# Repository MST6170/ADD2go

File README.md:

# ADD2go

**Wireless Fernanzeige für Dinamica Generale ADD2 / Siloking Mischwagen**

Überträgt Gewichtsdaten kabellos von der Mischwagen-Waage zum Radlader-Display oder Smartphone.

ADD2go ist in erster Linie eine **Fernanzeige** für die ADD2 Waage. Zusätzlich integriert ist eine **Schaufel-Wiegung** mit Drucksensor — fand ich nützlich, daher ist sie mit reingewandert.

*ADD2go — kabellose Fernanzeige für die ADD2-Waage*

---

## 📋 Übersicht

ADD2go besteht aus zwei ESP32-Modulen und einer optionalen WebApp:

| Modul | Standort | Funktion |
|-------|----------|----------|
| **Sender** | Mischwagen | Liest RS232 von ADD2 Waage, sendet per WiFi |
| **Empfänger** | Radlader | Zeigt Gewicht auf TFT-Display an |
| **WebApp** | Smartphone | Gewicht im Browser anzeigen |

> 💡 **Hinweis zur Hardware:** Sender und Empfänger nutzen **dieselbe Platine** — sie wird je nach Anwendung unterschiedlich bestückt (Sender: MAX3232 + WI-NET; Empfänger: zusätzlich TFT-Header, ADS1115-Header, K7812M für Drucksensor). Details siehe [`add2go_pcb/README.md`](add2go_pcb/README.md).

### Features

**Sender:**
- ✅ RS232 Auswertung des ADD2 Protokolls
- ✅ WiFi Access Point ("ADD2go")
- ✅ WiFi-Manager - zusätzlich mit Heimnetz verbinden
- ✅ mDNS - erreichbar unter `http://add2go.local`
- ✅ UDP Broadcast für Hardware-Empfänger
- ✅ WebSocket Server für WebApp
- ✅ Eingebaute WebApp mit TOTAL/ZERO Funktion
- ✅ "OFF" Erkennung wenn Waage ausgeschaltet
- ✅ Hardware Watchdog (kein Aufhängen)

**Empfänger:**
- ✅ Echtzeit-Gewichtsanzeige
- ✅ TOTAL/ZERO Funktion (Auto-Reset bei Verbindungsverlust)
- ✅ Schaufel-Wiegung mit Drucksensor (optional)
- ✅ Filter für stabile Anzeige (Mittelwert + Hysterese)
- ✅ ADS1115-Watchdog (Sensor-Ausfall wird erkannt)
- ✅ Auto-Reconnect bei WiFi-Verlust
- ✅ Hardware Watchdog

---

## 🌐 WiFi-Manager

Der Sender kann sich zusätzlich mit einem externen WLAN (z.B. Hof-WLAN) verbinden. Dadurch muss das Handy nicht mehr ins "ADD2go" WLAN wechseln.

### Einrichtung

1. Handy mit WLAN **"ADD2go"** verbinden
2. Browser öffnen: `http://192.168.4.1/setup`
3. Verfügbare Netzwerke werden angezeigt
4. Netzwerk auswählen, Passwort eingeben
5. Nach erfolgreicher Verbindung: erreichbar unter `http://add2go.local`

### Betriebsmodi

| Modus | Beschreibung |
|-------|--------------|
| **Nur AP** | Standard - Sender erstellt eigenes WLAN "ADD2go" |
| **AP + Station** | Sender ist zusätzlich mit Heimnetz verbunden |

### Vorteile der Heimnetz-Verbindung

- Kein WLAN-Wechsel mehr nötig am Handy
- Erreichbar unter `http://add2go.local` (mDNS)
- WLAN-Daten werden gespeichert (überlebt Neustart)
- Auto-Reconnect wenn Mischwagen zurückkommt
- AP "ADD2go" bleibt zusätzlich aktiv (Fallback)

---

## 🔧 Hardware

### Sender (Mischwagen)

*Sender-Modul: ESP32, MAX3232 (RS232) und 7805-Spannungsregler*

| Komponente | Typ | Bemerkung |
|------------|-----|-----------|
| Mikrocontroller | [ESP32-WROOM-32U](https://www.amazon.de/dp/B0F65KPWYR) | Mit U.FL Antennenanschluss |
| Antenne | 2.4GHz extern | Im ESP32-Set enthalten |
| RS232 Wandler | MAX3232CPE | DIP-16, 5x 1µF Kondensatoren |
| Spannungsregler | K7805M | 12V → 5V Schaltregler (pin-kompatibel zu 7805, kein Kühlkörper nötig) |
| Verpolschutz | 1N5822 | Schottky-Diode |
| Überspannungsschutz | 1.5KE18A | TVS-Diode 18V |
| WI-NET Stecker | Binder M16 5-pol | Bestellnr. 09 0313 00 05 |
| Gehäuse | [Industrie-Gehäuse 100×68×50 mm](https://de.aliexpress.com/item/1005005622148025.html) | gekauft (kein 3D-Druck nötig) |
| Platine | Custom KiCad-Projekt | Schaltplan, Layout, Fertigung — siehe [`add2go_pcb/README.md`](add2go_pcb/README.md) |

**Pinbelegung Sender:**

| ESP32 Pin | Funktion |
|-----------|----------|
| GPIO16 | RX2 ← MAX3232 (Daten von Waage) |
| GPIO17 | TX2 → MAX3232 (nicht verwendet) |
| 5V | Versorgung vom Spannungsregler |
| GND | Gemeinsame Masse |

*ESP32-WROOM-32 Pinbelegung (Referenz)*

### Empfänger (Radlader)

*Empfänger-Modul: ESP32, ILI9341 Display mit Touch und ADS1115 ADC*

| Komponente | Typ | Bemerkung |
|------------|-----|-----------|
| Mikrocontroller | [ESP32-WROOM-32U](https://www.amazon.de/dp/B0F65KPWYR) | Mit U.FL Antennenanschluss |
| Antenne | 2.4GHz extern | Im ESP32-Set enthalten |
| Display | [ILI9341 3.2" TFT](https://de.aliexpress.com/item/1005003005216533.html) | 320x240, SPI, mit Touch |
| Touch | XPT2046 | Resistiv, im Display integriert |
| ADC | ADS1115 | 16-bit, I²C (für Schaufel-Wiegung) |
| Drucksensor | [XIDIBEI 0-300 bar](https://de.aliexpress.com/item/4001002862246.html) | 9-36V Versorgung, 0.5-4.5V Ausgang (für Schaufel-Wiegung, optional) |
| Reed-Kontakt | Digital | Wiegeposition erkennen (optional) |
| Spannungsregler 5 V | K7805M | 12 V → 5 V Schaltregler (für ESP32) |
| Spannungsregler 12 V | K7812M | stabilisierte 12 V (für Drucksensor) |
| Gehäuse | 3D-gedruckt | STL-Dateien, Schalter, Kabelverschraubung — siehe [`case/README.md`](case/README.md) |
| Platine | Custom KiCad-Projekt | Schaltplan, Layout, Fertigung — siehe [`add2go_pcb/README.md`](add2go_pcb/README.md) |

**Pinbelegung Empfänger:**

| ESP32 Pin | Funktion |
|-----------|----------|
| GPIO5 | Display CS |
| GPIO2 | Display RST |
| GPIO4 | Display DC |
| GPIO23 | SPI MOSI |
| GPIO18 | SPI SCK |
| GPIO19 | SPI MISO |
| GPIO15 | Touch CS |
| GPIO14 | Touch IRQ |
| GPIO21 | I²C SDA (ADS1115) |
| GPIO22 | I²C SCL (ADS1115) |
| GPIO36 | Reed-Kontakt (LOW = Wiegeposition) |

*XIDIBEI Drucksensor (0–300 bar, 9–36 V → 0,5–4,5 V) — Quelle für die Schaufel-Wiegung*

### WI-NET Stecker (ADD2 Waage)

Der WI-NET Anschluss ist ein 5-poliger M16 Stecker an der ADD2 Waage.

**Passender Kabelstecker:** [Binder Serie 680, M16, 5-polig](https://www.binder-connector.de/de/produkte/rundsteckverbinder/m16-ip40-serie-680/kabelstecker-09-0313-00-05)
- Bestellnummer: **09 0313 00 05**
- Lötkontakte, 3.0-6.0mm Kabeldurchlass

> 💡 **Hinweis:** Bei diesem Stecker bin ich mir nicht 100% sicher — er passt nicht ganz exakt in die Buchse, funktioniert aber zuverlässig.

Die Pinbelegung wurde durch eigene Messungen ermittelt:

| Pin | Position | Funktion | Verbindung |
|-----|----------|----------|------------|
| 1 | unten | +12V | → Spannungsregler VIN |
| 2 | rechts oben | GND | → Gemeinsame Masse |
| 3 | oben mitte | TX | → MAX3232 R1IN (Pin 13) |
| 4 | links oben | - | nicht belegt |
| 5 | links unten | - | nicht belegt |

*WI-NET Stecker (Binder M16, 5-polig) — eigene Messung der Pinbelegung*

> ⚠️ **Wichtig:** Pinbelegung von vorne auf die Buchse (an der Waage) gesehen!

---

## 📡 Kommunikation

### WiFi Konfiguration

| Parameter | Wert |
|-----------|------|
| AP SSID | `ADD2go` |
| AP Passwort | keins (offen) |
| AP IP | `192.168.4.1` |
| AP Subnetz | `255.255.255.0` |
| mDNS Hostname | `add2go.local` |
| WiFi Modus | APSTA (AP + Station gleichzeitig) |

### Netzwerk-Protokolle

| Protokoll | Port | Richtung | Verwendung |
|-----------|------|----------|------------|
| UDP Broadcast | 5005 | Sender → Empfänger | Hardware-Display |
| WebSocket | 81 | Sender ↔ Browser | WebApp (bidirektional) |
| HTTP | 80 | Browser → Sender | WebApp + Setup-Seite |

### UDP Protokoll (für Hardware-Empfänger)

Der Sender sendet alle 100ms (10 Hz) einen UDP-Broadcast:

| Parameter | Wert |
|-----------|------|
| Ziel-IP | `192.168.4.255` (Broadcast) |
| Port | `5005` |
| Format | ASCII String |

**Nachrichten:**

| Nachricht | Bedeutung |
|-----------|-----------|
| `1234` | Gewicht in kg (ohne Einheit) |
| `OFF` | Waage ist ausgeschaltet |

### WebSocket Protokoll (für WebApp)

Der Sender sendet alle 100ms (10 Hz) an alle verbundenen WebSocket-Clients:

| Parameter | Wert |
|-----------|------|
| Port | `81` |
| Format | `Gewicht\|RSSI` |

**Beispiele:**

| Nachricht | Bedeutung |
|-----------|-----------|
| `1234\|-65` | 1234 kg, Signalstärke -65 dBm |
| `OFF\|-70` | Waage aus, Signalstärke -70 dBm |

---

## 📟 RS232 Protokoll (ADD2 Waage)

Das RS232 Protokoll wurde durch eigenes Reverse-Engineering ermittelt.

### Schnittstellenparameter

| Parameter | Wert |
|-----------|------|
| Baudrate | 19200 |
| Datenbits | 8 |
| Parität | Keine |
| Stoppbits | 1 |
| Updaterate | ~1.3 Hz (alle ~770ms) |

### Frame-Struktur

Die Waage sendet kontinuierlich Frames mit folgendem Aufbau:

```
[Präambel] [Start] [Type] [Seq] [Header] [Gewicht ASCII] [Ende]
    16       0x23   0x03   xx    0x18 0x00    "  1234"     0x0A
```

| Feld | Bytes | Wert | Beschreibung |
|------|-------|------|--------------|
| Präambel | 16 | variabel | Sync-Bytes (werden ignoriert) |
| Start | 1 | `0x23` | Start-Marker (`#`) |
| Type | 1 | `0x03` | Frame-Typ (ETX) |
| Sequence | 1 | `0x00-0xFF` | Laufender Zähler |
| Header | 2 | `0x18 0x00` | Fester Header |
| Gewicht | variabel | ASCII | Rechtsbündig mit Leerzeichen |
| Ende | 1 | `0x0A` | Line Feed (LF) |

### Beispiel-Frame

```
Hex:  23 03 7B 18 00 20 20 20 20 32 0A
      │  │  │  │  │  └──────────┴──┴── "    2" + LF = 2 kg
      │  │  │  └──┴── Header 0x18 0x00
      │  │  └── Sequence 0x7B (123)
      │  └── Type 0x03
      └── Start 0x23
```

### Gewichtswerte

| Anzeige Waage | RS232 Daten | Bedeutung |
|---------------|-------------|-----------|
| `2` | `20 20 20 20 32` | 2 kg |
| `123` | `20 20 31 32 33` | 123 kg |
| `1234` | `20 31 32 33 34` | 1234 kg |
| (aus) | keine Daten | Waage ausgeschaltet |

### OFF-Erkennung

Wenn 3 Sekunden lang keine gültigen RS232-Daten empfangen werden, gilt die Waage als ausgeschaltet. Der Sender sendet dann `"OFF"` über UDP und WebSocket.

---

## 💾 Installation

### Voraussetzungen

- Arduino IDE 1.8.19
- ESP32 Board Package (v3.x empfohlen)
- USB-Treiber für ESP32 (CP2102 oder CH340)

### Benötigte Libraries

**Sender:**
- WebSockets by Markus Sattler (Library Manager: "WebSockets")

**Empfänger:**
- TFT_eSPI by Bodmer
- XPT2046_Touchscreen by Paul Stoffregen
- Adafruit ADS1X15 by Adafruit

### TFT_eSPI Konfiguration

Die TFT_eSPI Library muss für das ILI9341 Display konfiguriert werden.

> ⚠️ **Wichtig:** Die TFT_eSPI Library hat eine **globale** Konfigurationsdatei (`User_Setup.h`). Diese wird von ALLEN Projekten geteilt, die TFT_eSPI verwenden! Wenn du an einem anderen Projekt arbeitest und die Pins änderst, läuft ADD2go nicht mehr — `tft.init()` hängt dann beim Boot ohne Fehlermeldung. **Daher: vor jedem Flashen prüfen, dass `User_Setup.h` zu ADD2go passt.**

**Datei:** `Arduino/libraries/TFT_eSPI/User_Setup.h`

```cpp
// Display-Treiber
#define ILI9341_DRIVER

// Display-Größe
#define TFT_WIDTH  240
#define TFT_HEIGHT 320

// Pin-Definitionen
#define TFT_CS   5
#define TFT_DC   4
#define TFT_RST  2
#define TFT_MOSI 23
#define TFT_SCLK 18
#define TFT_MISO 19

// SPI-Geschwindigkeit
#define SPI_FREQUENCY 40000000

// Touch
#define TOUCH_CS 15
```

### Flashen

**Sender:**
```
Board:     ESP32 Dev Module
Datei:     add2go_sender_v1_2_4/add2go_sender_v1_2_4.ino
Baudrate:  115200
```

**Empfänger:**
```
Board:     ESP32 Dev Module
Datei:     add2go_empfaenger_v1_0_2/add2go_empfaenger_v1_0_2.ino
Baudrate:  115200
```

---

## 🖥️ Bedienung

### Hardware-Display (Empfänger)

*Hauptansicht mit Gewichtszahl und TOTAL/ZERO-Buttons*

**Anzeigen:**

| Anzeige | Farbe | Bedeutung |
|---------|-------|-----------|
| Gewicht | Weiß | Normale Anzeige |
| `OFF` | Rot | Waage ausgeschaltet |
| `OFFLINE` | Rot | Keine WiFi-Verbindung zum Sender |
| `SUCHE..` | Orange | WiFi wird gesucht |
| `- - - -` | Grau | Verbunden, warte auf Daten |

**Buttons:**

| Button | Funktion |
|--------|----------|
| **TOTAL** | Zeigt Gesamt-Gewicht von Waage |
| **ZERO** | Setzt aktuelles Gewicht als Null (Differenz-Messung) |
| **Schaufel** | Öffnet Schaufel-Wiegung Menü |

> 💡 **Hinweis:** ZERO wird automatisch zurückgesetzt wenn die Verbindung zum Sender verloren geht oder die Waage auf OFF wechselt. So gibt es nach Wiedereinschalten keinen falschen Offset.

**Schaufel-Wiegung Menü:**

*Setup-Menü für die Schaufel-Wiegung*

| Menüpunkt | Funktion |
|-----------|----------|
| TARA | Setzt leere Schaufel als Nullpunkt |
| KALIBRIEREN | Bekanntes Gewicht eingeben zur Kalibrierung |
| FILTER | Mittelwert-Anzahl (5-30) und Hysterese-Schwelle (1-10 kg) |
| ZURÜCK | Zurück zur Hauptansicht |

> 💡 **Hinweis:** Bei TARA und Kalibrierung wird der Filter-Buffer automatisch geleert, damit die Anzeige sofort die neuen Werte zeigt.

**Sensor-Ausfall:** Wenn der ADS1115 nicht antwortet (z.B. Kabelbruch, Wackelkontakt), zeigt der Schaufel-Button `SENSOR-FEHLER` in rot an. TARA und KALIBRIEREN sind dann gesperrt.

---

## 📱 WebApp

Der Sender bietet eine eingebaute WebApp - das Gewicht direkt auf dem Smartphone anzeigen. Sie funktioniert parallel zum Hardware-Empfänger und ist als Nebenfunktion gedacht.

<p align="center">
  
  <br>
  <em>WebApp im Browser am Smartphone</em>
</p>

### Zugriff

| Methode | URL | Wann nutzen |
|---------|-----|-------------|
| Direkt | `http://192.168.4.1` | Handy mit "ADD2go" WLAN verbunden |
| Heimnetz | `http://add2go.local` | Handy im Hof-WLAN (nach Setup) |
| Heimnetz | `http://[IP-Adresse]` | Falls mDNS nicht funktioniert |

### Funktionen

| Element | Beschreibung |
|---------|--------------|
| **Gewichtsanzeige** | Groß und zentral, mit "kg" Einheit |
| **TOTAL** | Zeigt Gesamtgewicht von der Waage |
| **ZERO** | Speichert aktuelles Gewicht, zeigt Differenz |
| **Signalstärke** | 📶▂▄▆█ (4 Stufen) |
| **Status** | 🟢 Verbunden / 🟠 Waage aus / 🔴 Offline |

### TOTAL / ZERO Funktion

- **TOTAL**: Normaler Modus - zeigt das Gewicht wie es von der Waage kommt
- **ZERO**: Drücken um aktuelles Gewicht als Nullpunkt zu setzen. Danach wird die Differenz angezeigt. Praktisch zum Wiegen von Zuladungen.

Der aktive Modus ist **orange** markiert. Diese Funktion läuft lokal in der WebApp und beeinflusst nicht die ADD2 Waage selbst.

---

## 🔍 Troubleshooting

### Häufige Probleme

| Problem | Ursache | Lösung |
|---------|---------|--------|
| Boot-Loop, hängt bei `tft.init()` | Falsches `User_Setup.h` (z.B. von anderem Projekt überschrieben) | `User_Setup.h` der TFT_eSPI Library prüfen, Pins müssen zu ADD2go passen |
| Display zeigt `OFFLINE` | Kein WiFi zum Sender | Sender einschalten, Nähe prüfen, Antennen prüfen |
| Display zeigt `OFF` | Waage ausgeschaltet | ADD2 Waage einschalten |
| Display zeigt `- - - -` | WiFi ok, aber keine Daten | RS232 Verkabelung prüfen |
| Schaufel: `SENSOR-FEHLER` | ADS1115 antwortet nicht | I²C Verkabelung prüfen, Neustart |
| WebApp zeigt `---` | WebSocket nicht verbunden | Seite neu laden, WLAN prüfen |
| WebApp Buttons grau | Keine Verbindung | Warten oder Seite neu laden |
| `add2go.local` geht nicht | mDNS Problem | IP-Adresse direkt verwenden |
| WLAN-Daten nicht gespeichert | NVS Fehler | Serial Monitor prüfen |
| Sender startet neu | Watchdog | Serial Monitor auf Fehler prüfen |

### Serial Monitor Debug

Baudrate: **115200**

**Sender Startup (normal):**
```
========================================
ADD2go Sender - v1.2.4
========================================

[NVS] Lade gespeicherte Daten...
[NVS] SSID: MeinHofWLAN
[NVS] Passwort: (gespeichert)
[NVS] Auto-Connect: JA
[OK] RS232 gestartet (19200 Baud, GPIO16)
[OK] Watchdog: 10 Sekunden
[OK] WiFi AP gestartet: ADD2go
[OK] AP IP: 192.168.4.1
[STA] Verbinde mit: MeinHofWLAN
....
[STA] Verbunden! IP: 192.168.1.38
[OK] mDNS: http://add2go.local
[OK] UDP Port: 5005
[OK] WebServer gestartet (Port 80)
[OK] WebSocket gestartet (Port 81)

=========== ZUGRIFF ===========
Im ADD2go WLAN:
  WebApp:  http://192.168.4.1
  Setup:   http://192.168.4.1/setup

Im Heimnetz (mDNS):
  WebApp:  http://add2go.local
  Setup:   http://add2go.local/setup
  oder:    http://192.168.1.38
===============================

Warte auf ADD2 Waage...
```

**Sender Betrieb:**
```
[RS232] Gewicht: 1234 kg
[UDP] Gesendet: "1234" (1 AP Clients)
[WS] Client #0 verbunden
[STATUS] AP Clients: 1 | WS Clients: 1 | STA: MeinHofWLAN (192.168.1.38)
```

**Empfänger Startup:**
```
========================================
ADD2go Empfaenger - v1.0.1
========================================

[OK] Reed-Kontakt GPIO36 konfiguriert
[OK] ADS1115 gefunden
[OK] NVS geladen - Tara: 0.500V, Faktor: 100.0 kg/V
[OK] Display initialisiert
[OK] Touch initialisiert
[OK] Watchdog: 5 Sekunden
[OK] WiFi verbunden! IP: 192.168.4.2
[OK] UDP Port: 5005
```

---

## 📁 Projektstruktur

```
ADD2go/
├── add2go_sender_v1_2_4/
│   └── add2go_sender_v1_2_4.ino         # Sender Firmware
├── add2go_empfaenger_v1_0_2/
│   └── add2go_empfaenger_v1_0_2.ino     # Empfänger Firmware
├── add2go_pcb/                           # KiCad-Projekt für die Universal-Platine (Sender / Empfänger)
├── case/                                 # 3D-Druck-STLs für Empfänger-Gehäuse
├── images/                               # Bilder & Pinout-Diagramme
├── User_Setup.h                          # TFT_eSPI-Vorlage (in Library kopieren)
├── CLAUDE.md                             # Kurzdoku für KI-Assistenten
├── README.md                             # Diese Dokumentation
├── LICENSE                               # CC BY-NC-SA 4.0
└── .gitignore                            # Git Ignore-Liste
```

---

## 📜 Changelog

### Sender

#### v1.2.4 (Januar 2026)
- Fix: Watchdog früher initialisieren (vor WLAN-Warteschleife)
- Fix: idle_core_mask konservativer (nur loopTask überwachen)
- Fix: JSON SSID Escaping bei Sonderzeichen

#### v1.2.3 (Januar 2026)
- WebApp: TOTAL/ZERO Buttons hinzugefügt
- WebApp: Gewicht mit "kg" Einheit
- WebApp: Cleaner UI

#### v1.2.2 (Januar 2026)
- mDNS Support (`http://add2go.local`)
- Warten auf WLAN-Verbindung beim Boot (max 15 Sek)
- Bessere Debug-Ausgaben für NVS

#### v1.2.1 (Januar 2026)
- Async WLAN-Scan (verhindert Watchdog-Trigger)
- Robustere loop() mit mehrfachen WDT-Resets
- RS232 Byte-Limit pro Loop (max 256)

#### v1.2.0 (Januar 2026)
- WiFi-Manager WebUI unter `/setup`
- APSTA Modus (AP + Station gleichzeitig)
- WLAN-Daten persistent in NVS gespeichert
- Auto-Reconnect bei Verbindungsverlust

#### v1.1.0 (Januar 2026)
- WebSocket Server für Browser/Handy
- Eingebettete WebApp
- Signalstärke-Anzeige

#### v1.0.0 (Januar 2026)
- Erste stabile Release
- RS232 Protokoll-Auswertung
- UDP Broadcast
- Hardware Watchdog
- OFF-Erkennung

### Empfänger

#### v1.0.2 (Mai 2026)
- NEU: Signalstärke-Anzeige (4 Balken) links vom WiFi-Status-Punkt
- Fix: SENSOR-FEHLER-Anzeige passt jetzt in den Schaufel-Button (zentriert, ohne "Schaufel:"-Präfix)

#### v1.0.1 (Mai 2026)
- Fix: ZERO-Modus wird automatisch zurückgesetzt bei OFF oder Verbindungsverlust
- Fix: Filter-Buffer wird nach TARA/Kalibrierung geleert (verhindert Mischwerte)
- Fix: ADS1115-Watchdog erkennt Sensor-Ausfall und zeigt Warnung
- Fix: Exakte Button-Zentrierung mit `tft.textWidth()`

#### v1.0.0 (Januar 2026)
- Erste stabile Release
- TFT Display mit Touch
- TOTAL/ZERO Funktion
- Schaufel-Wiegung mit ADS1115
- Filter (Mittelwert + Hysterese)
- Hardware Watchdog
- Boot-Screen mit Fortschrittsbalken

---

## ⚠️ Disclaimer

Dieses Projekt ist ein privates DIY-Projekt. Die Verwendung erfolgt auf eigene Gefahr.

- "ADD2", "Dinamica Generale" und "Siloking" sind Marken der jeweiligen Eigentümer
- Das RS232 Protokoll wurde durch eigenes Reverse-Engineering ermittelt
- Keine Garantie auf Funktionalität oder Kompatibilität
- Nicht für sicherheitskritische Anwendungen geeignet
- Änderungen am Fahrzeug können Gewährleistung beeinflussen

---

## 📄 Lizenz

Dieses Projekt ist lizenziert unter [Creative Commons Attribution-NonCommercial-ShareAlike 4.0 International](https://creativecommons.org/licenses/by-nc-sa/4.0/).

**Das bedeutet:**
- ✅ Teilen und Anpassen erlaubt
- ✅ Namensnennung erforderlich
- ❌ Kommerzielle Nutzung verboten
- 🔄 Änderungen müssen unter gleicher Lizenz stehen

---

**Hardware & Software:** MST 2026

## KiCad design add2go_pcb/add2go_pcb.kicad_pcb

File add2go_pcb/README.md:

# ADD2go PCB

*Fertiges Empfänger-Modul auf Basis dieser Platine*

## Übersicht

Universelle Platine für ADD2go — kann je nach **Bestückung** entweder als
**Sender** (im Mischwagen, Anschluss an die ADD2-Waage über RS232) oder als
**Empfänger** (im Radlader, mit TFT-Display und Drucksensor für die
Schaufel-Wiegung) verwendet werden. Beide Varianten teilen das gleiche Board.

## Status

**Version 1** — bestellt bei JLCPCB, getestet, läuft produktiv.

## Features

- RS232-Pegelwandlung mit MAX3232 (Sender-Bestückung, für die ADD2-Waage)
- 12 V → 5 V Versorgung mit K7805M Schaltregler (für ESP32)
- 12 V stabilisiert mit K7812M (für Drucksensor in Empfänger-Bestückung)
- Verpolschutz mit 1N5822 Schottky-Diode
- TVS-Überspannungsschutz mit 1.5KE18A (18 V)
- Eingangs-Sicherung
- M16-Anschluss zur Waage (5-polig, WI-NET)
- Sockel für ESP32-WROOM-32U
- Header für TFT 3.2" Display (Empfänger-Bestückung)
- Header für ADS1115 ADC-Modul (Empfänger-Bestückung)
- Reine THT-Bestückung (Through-Hole), keine SMD-Bauteile

## Komponenten

*Bestückte Platine in Empfänger-Konfiguration*

| Bauteil | Typ | Funktion | Bestückt bei |
|---|---|---|---|
| ESP32-Sockel | Pin-Header 10 + 19 | Modulträger ESP32-WROOM-32U | Sender + Empfänger |
| MAX3232 | Interface-IC | RS232-Pegelwandler | nur Sender |
| K7805M-1000R3 | Mornsun Schaltregler | 12 V → 5 V (~95 % Wirkungsgrad) | Sender + Empfänger |
| K7812M-1000R3 | Mornsun Schaltregler | 12 V stabilisiert (für Drucksensor) | nur Empfänger |
| 1N5822 | Schottky-Diode | Verpolschutz Eingang | Sender + Empfänger |
| 1.5KE18A | TVS-Diode 18 V | Überspannungsschutz | Sender + Empfänger |
| Sicherung | Fuse | Eingangsschutz | Sender + Empfänger |
| Elkos | 100 µF / 16 V, 470 µF | Pufferkondensatoren Versorgung | Sender + Empfänger |
| Kerkos | 100 nF (mehrfach) | MAX3232-Ladekondensatoren + Stützkapazitäten | applikationsabhängig |
| 4k7, 10k | Widerstand | Pull-up / Pull-down | applikationsabhängig |

## Steckverbinder

| Header | Pinzahl | Funktion |
|---|---|---|
| WI-NET (M16) | 5-polig | Anschluss an die ADD2-Waage (Sender) bzw. Versorgung (Empfänger) |
| TFT | 14-polig | ILI9341 3.2" Display + Touch (nur Empfänger-Bestückung) |
| ADS1115 | 6-polig | I²C-Modul für Drucksensor (nur Empfänger-Bestückung) |
| ESP32 | 10 + 19 | Sockel für das ESP32-WROOM-32U-Modul |

> 📌 Pinbelegung des **WI-NET-Steckers** und alle **ESP32-Pin-Zuordnungen** stehen in der [Haupt-README](../README.md).

## Spannungsversorgung

- **Eingang**: 12 V vom WI-NET-Stecker (Bordnetz des Mischwagens / Radladers, real 11–14 V mit Schwankungen)
- Eingangsschutz: Sicherung → TVS (1.5KE18A, 18 V) → 1N5822 Schottky (Verpolschutz)
- **5 V Schiene** (für ESP32): K7805M Schaltregler — kein Kühlkörper nötig (~95 % Wirkungsgrad), weiter Eingangsspannungsbereich, robust gegen Bordnetz-Schwankungen
- **12 V Schiene stabilisiert** (nur Empfänger): K7812M für den XIDIBEI-Drucksensor (9–36 V Versorgungsbereich), liefert sauberere 12 V als das Bordnetz direkt

## Fertigung

| Parameter | Wert |
|---|---|
| Lagen | 2 (F.Cu / B.Cu) |
| Boardgröße | **59 × 68 mm** |
| Boardstärke | 1.6 mm (Standard) |
| Bestückung | reine THT (Through-Hole), manuell |
| Hersteller | bei JLCPCB bestellt |

| Vorderseite | Rückseite |
|---|---|
|  |  |

Gerber- und Drill-Files sind **nicht** im Repo enthalten — bei Bedarf in KiCad über *File → Plot* (Layer F.Cu, B.Cu, F.Mask, B.Mask, F.SilkS, B.SilkS, Edge.Cuts) und *File → Fabrication Outputs → Drill Files* exportieren.

## Dateien im Ordner

| Datei | Bedeutung |
|---|---|
| `add2go_pcb.kicad_pro` | KiCad-Projektdatei (Einstellungen, DRC-Regeln) |
| `add2go_pcb.kicad_sch` | Schaltplan (Eeschema) |
| `add2go_pcb.kicad_pcb` | PCB-Layout (Pcbnew) |

Projekt öffnen mit **KiCad 9.x** über `add2go_pcb.kicad_pro`.

> Hinweis: KiCad legt zusätzlich `*.kicad_prl`-Dateien an — die enthalten lokale User-Einstellungen (zuletzt geöffnete Tabs, Fenster-Layout) und sind über `.gitignore` ausgeschlossen.

## Querverweis

Für den Gesamtkontext (ESP32-Pinbelegung, RS232-Protokoll der ADD2-Waage,
Pinbelegung des WI-NET-Steckers, vollständige Komponentenliste des Projekts):
siehe [Haupt-README](../README.md).

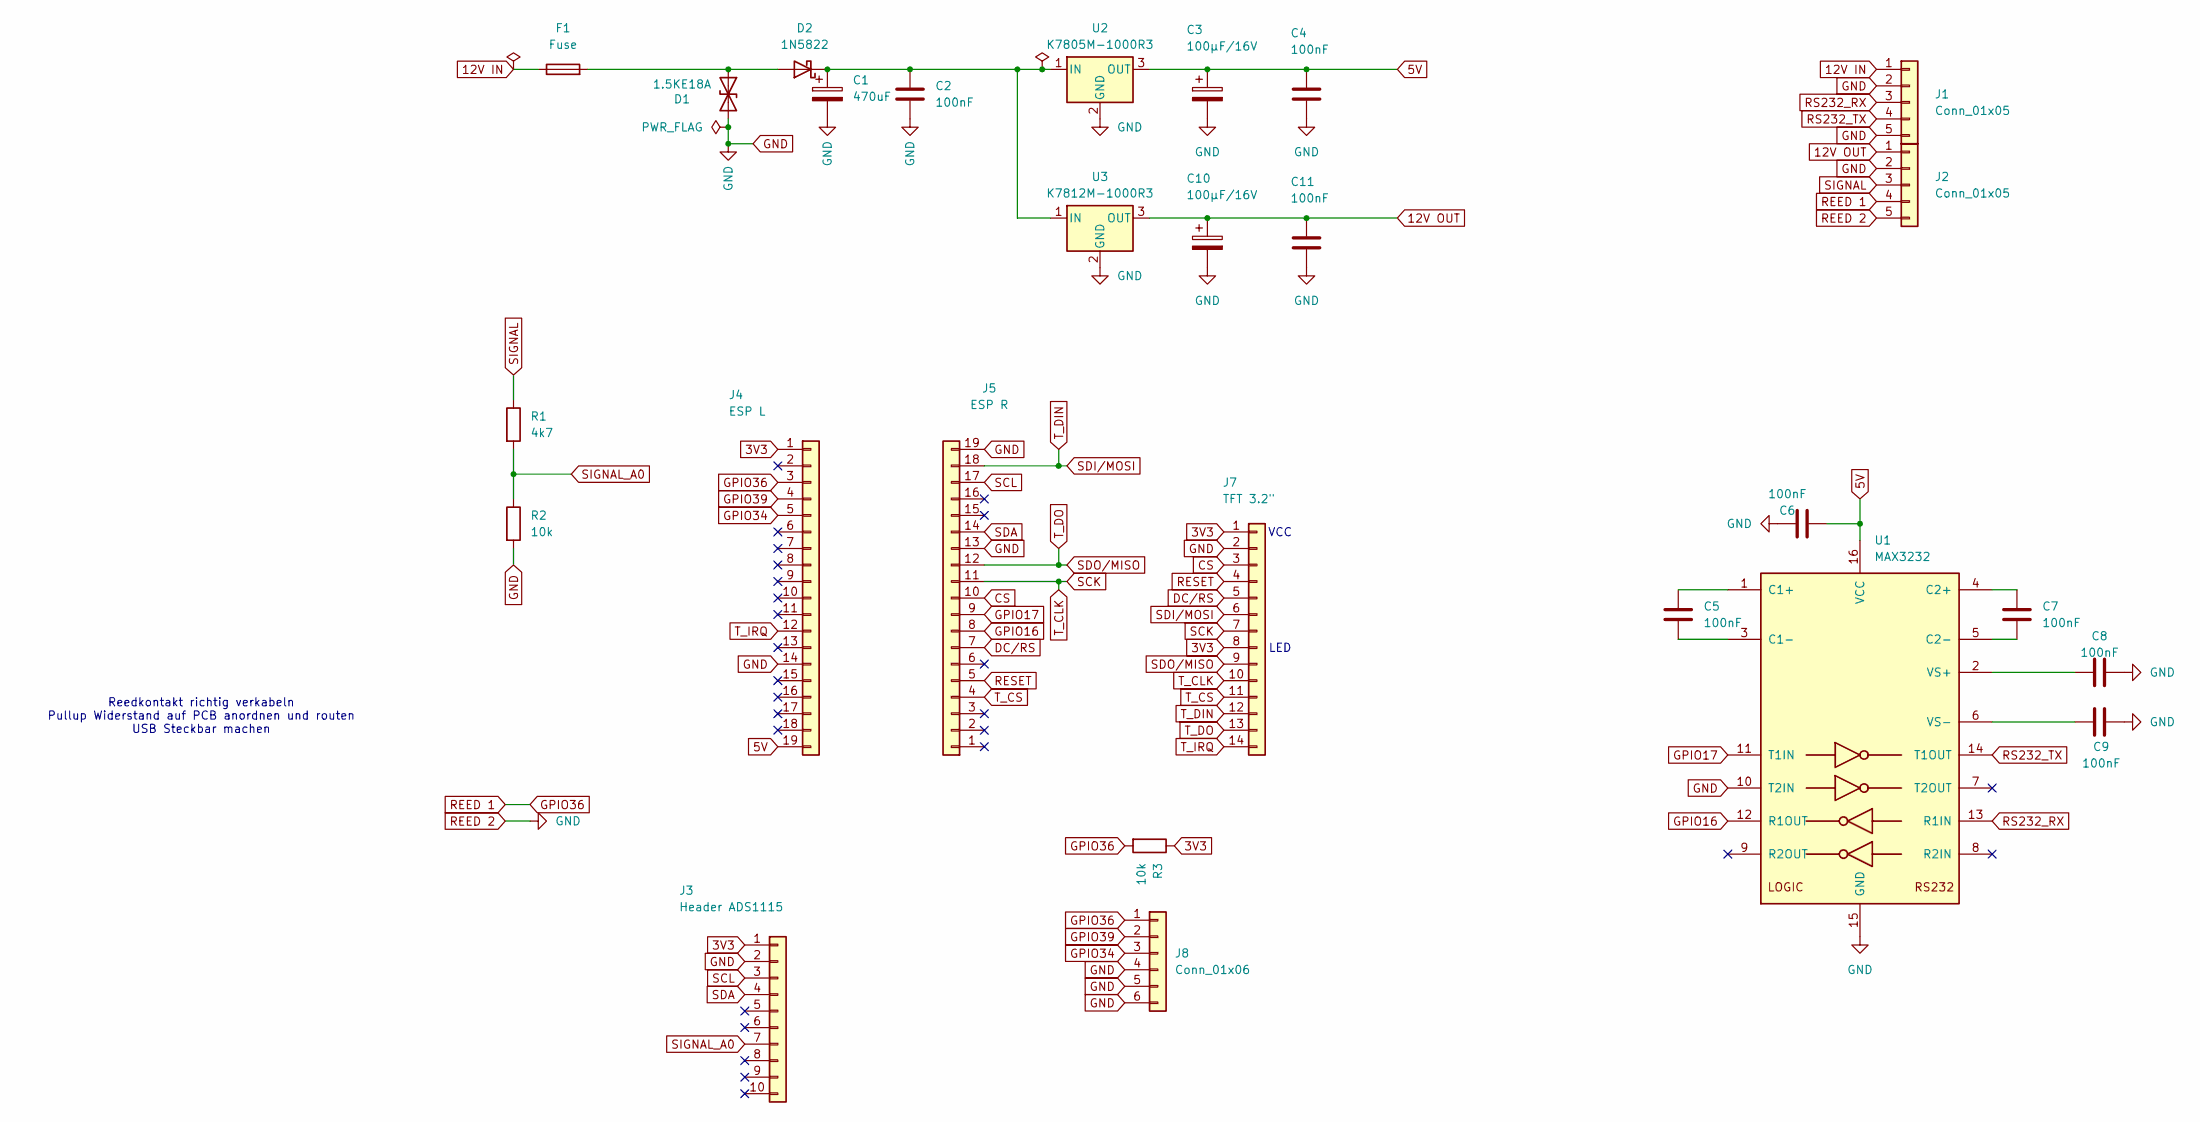
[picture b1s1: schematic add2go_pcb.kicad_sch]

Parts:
C1: 470uF; CP_Radial_D10.0mm_P5.00mm
C2, C4, C5, C6, C7, C8, C9, C11: 100nF; C_Disc_D5.0mm_W2.5mm_P2.50mm
C3, C10: 100µF/16V; CP_Radial_D6.3mm_P2.50mm
D1: 1.5KE18A; D_DO-201AD_P15.24mm_Horizontal
D2: 1N5822; D_DO-201AD_P15.24mm_Horizontal
F1: Fuse; FuseHolder_ATO_20mm_THT_2x2
J1, J2: Conn_01x05; JST_VH_B5P-VH_1x05_P3.96mm_Vertical
J3: Header ADS1115; PinHeader_1x10_P2.54mm_Vertical
J4: ESP L; PinHeader_1x19_P2.54mm_Vertical
J5: ESP R; PinHeader_1x19_P2.54mm_Vertical
J7: TFT 3.2"; PinHeader_1x14_P2.54mm_Vertical
J8: Conn_01x06; PinHeader_1x06_P2.54mm_Vertical
R1: 4k7; R_Axial_DIN0207_L6.3mm_D2.5mm_P10.16mm_Horizontal
R2, R3: 10k; R_Axial_DIN0207_L6.3mm_D2.5mm_P10.16mm_Horizontal
U1: MAX3232; DIP-16_W7.62mm
U2: K7805M-1000R3; Converter_DCDC_RECOM_R-78E-0.5_THT; LCSC C5279984
U3: K7812M-1000R3; Converter_DCDC_RECOM_R-78E-0.5_THT; LCSC C5279984

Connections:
3V3: J3.1, J4.1, J7.1, J7.8, R3.1
5V: C3.1, C4.1, C6.1, J4.19, U1.16 (VCC), U2.3 (OUT)
12V IN: F1.1, J1.1
12V OUT: C10.1, C11.1, J2.1, U3.3 (OUT)
CS: J5.10, J7.3
DC/RS: J5.7, J7.5
GND: C1.2, C2.2, C3.2, C4.2, C6.2, C8.2, C9.2, C10.2, C11.2, D1.2 (A2), J1.2, J1.5, J2.2, J2.5, J3.2, J4.14, J5.13, J5.19, J7.2, J8.4, J8.5, J8.6, R2.2, U1.10 (T2IN), U1.15 (GND), U2.2 (GND), U3.2 (GND)
GPIO16: J5.8, U1.12 (R1OUT)
GPIO17: J5.9, U1.11 (T1IN)
GPIO34: J4.5, J8.3
GPIO36: J2.4, J4.3, J8.1, R3.2
GPIO39: J4.4, J8.2
unnamed: D1.1 (A1), D2.2 (A), F1.2
unnamed: C1.1, C2.1, D2.1 (K), U2.1 (IN), U3.1 (IN)
unnamed: C5.1, U1.1 (C1+)
unnamed: C5.2, U1.3 (C1-)
unnamed: C7.1, U1.4 (C2+)
unnamed: C7.2, U1.5 (C2-)
unnamed: C8.1, U1.2 (VS+)
unnamed: C9.1, U1.6 (VS-)
RESET: J5.5, J7.4
RS232_RX: J1.3, U1.13 (R1IN)
RS232_TX: J1.4, U1.14 (T1OUT)
SCK: J5.11, J7.7, J7.10
SCL: J3.3, J5.17
SDA: J3.4, J5.14
SDI/MOSI: J5.18, J7.6, J7.12
SDO/MISO: J5.12, J7.9, J7.13
SIGNAL: J2.3, R1.1
SIGNAL_A0: J3.7, R1.2, R2.1
T_CS: J5.4, J7.11
T_IRQ: J4.12, J7.14

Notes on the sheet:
LED
Reedkontakt richtig verkabeln Pullup Widerstand auf PCB anordnen und routen USB Steckbar machen
VCC

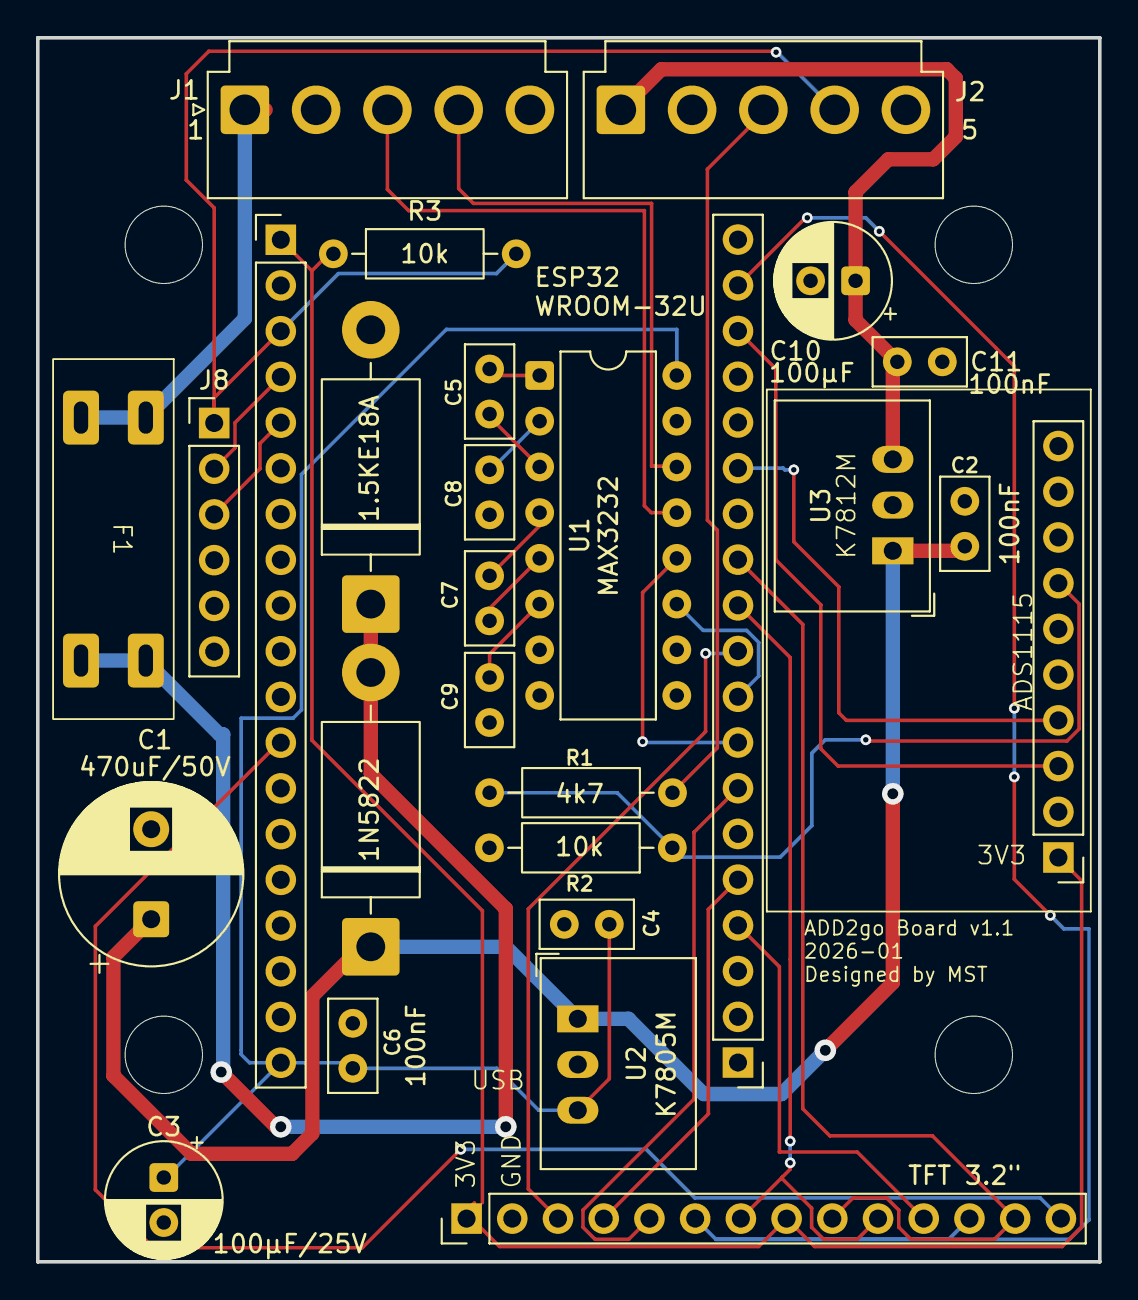
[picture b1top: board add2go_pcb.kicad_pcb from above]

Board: 2 copper layers, 59.0 x 68.0 mm, 27 parts (0 on the bottom side), 32 nets.

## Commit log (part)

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2026-05-05 Repo aufgeraeumt: gitignore, Backups raus
2026-05-11 chore: gitignore for add2go_empfaenger_pio subfolder
2026-05-11 phase3c-1: add2go_empfaenger_pio skeleton + auto-push hook + regression checklist
2026-05-11 test: dummy file for hook delete smoke-test
2026-05-11 test: confirm hook -A flag stages deletions
2026-05-11 phase3c-3: sketch v1.0.2 migrated to modules (storage/state/network/scale/display/touch/ui)
2026-05-11 phase3c-4+5: tab-switch button + flow-tab with WebSocketsClient
    Schritt 4 — Tab-Switch-Button rechts oben (35x35), toggelt Schaufel <-> Flow.
    - Schaufel aktiv: dunkelblauer Wassertropfen (Ziel = Flow wechseln)
    - Flow aktiv: "ADD" / "2" zweizeilig rubinrot (Ziel = zurueck zu Schaufel)
    Schritt 5 — Flow-Tab mit WebSocketsClient zu add2flow.
    - flow_tab.{h,cpp}: WS-Logik, pipe-Parser (v1|STATE|done|target|lpm|preset|err|rssi|p1|p2|p3),
    State-Cache, Confirm-Modal-Logik, Touch-Routing.
2026-05-11 phase3c-6: doku finalisiert (HARDWARE/GOTCHAS/USER_FLOWS + README/CLAUDE update)
2026-05-11 phase3c-5: flow-tab selective redraw fix + presets without L
    - Flicker bei 10 Hz WS-Updates behoben: zeichneFlowTab macht jetzt full-draw nur bei Tab-Switch, updateFlowTab macht state-tracking + partial redraw pro Feld (Liter / L/min / Badge / Buttons).
    - Preset-Buttons zeigen nur Zahl (kein 'L'-Suffix) — passt fuer 3-stellige Liter-Werte in 70 px Buttons.
2026-05-12 phase3c-7: ADD2-button stays visible during FILLING
    drawFlowLiters fillRect war 0..320 breit — ueberzeichnete dabei die untere
    Haelfte des Tab-Switch-Buttons (x=283..318, y=30..65). Bei jedem Liter-Update
    verschwand der Button-Bottom. Fix: fillRect bis x=280 statt 320 (Liter-Text
    zentriert auf 160 bleibt sicher in 0..280-Range).
